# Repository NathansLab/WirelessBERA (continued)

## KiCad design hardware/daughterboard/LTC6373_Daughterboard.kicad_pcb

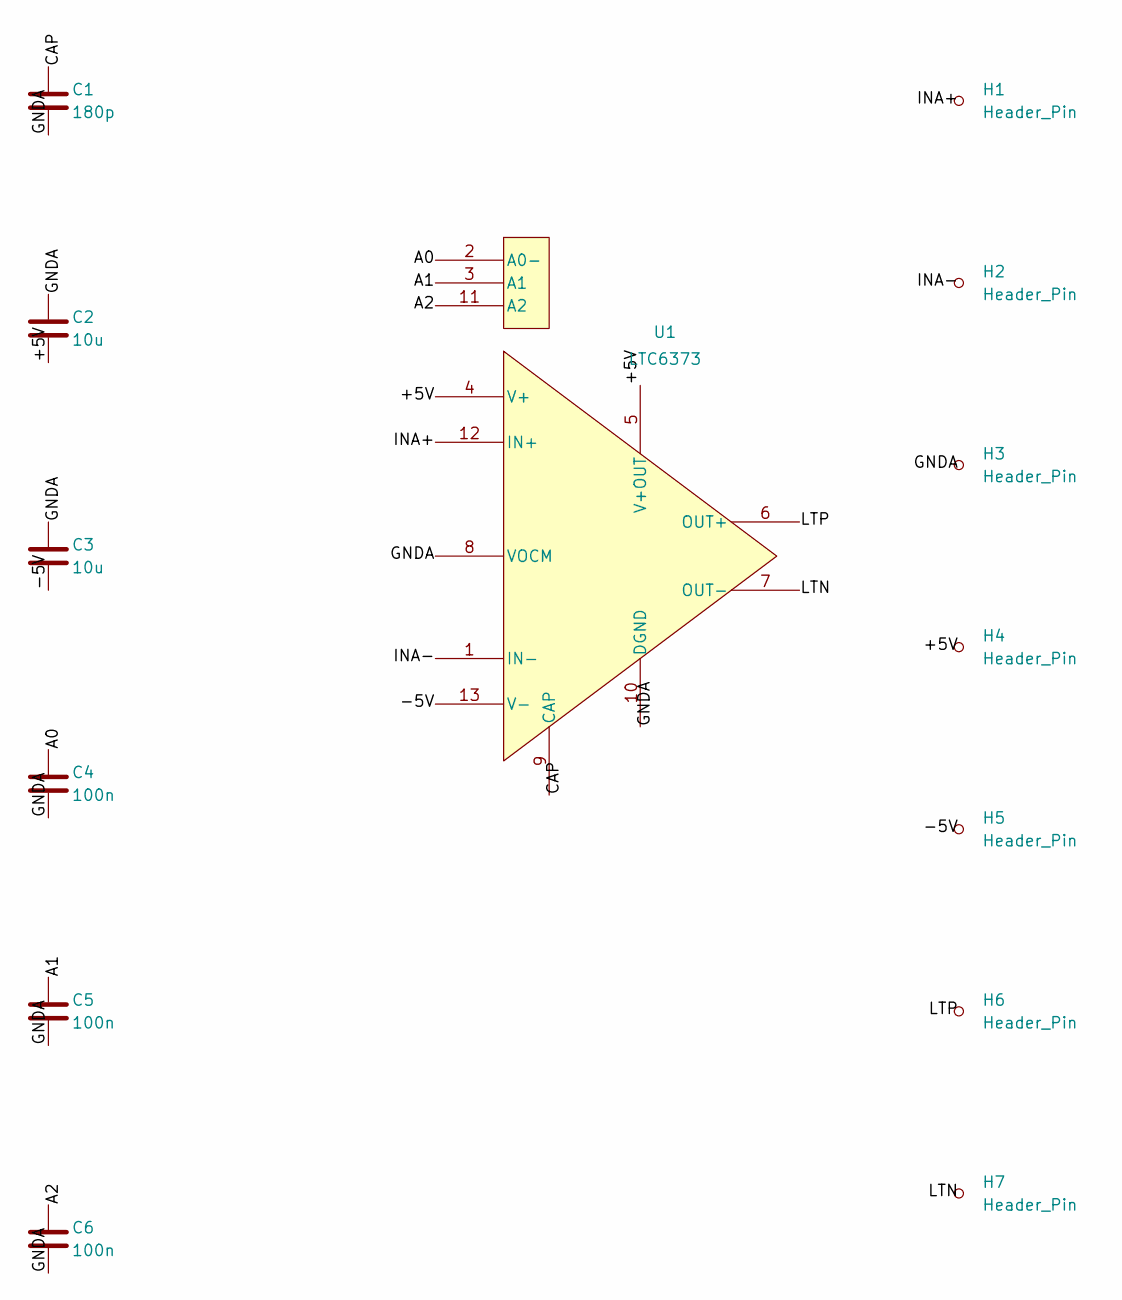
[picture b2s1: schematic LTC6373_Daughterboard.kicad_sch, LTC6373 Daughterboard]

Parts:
C1: 180p; C_0603_1608Metric
C2, C3: 10u; C_0603_1608Metric
C4, C5, C6: 100n; C_0603_1608Metric
H1, H2, H3, H4, H5, H6, H7: Header_Pin; TestPoint_Loop_D2.60mm_Drill0.9mm_Beaded
U1: LTC6373; LTC6373_DFN-12

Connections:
+5V: C2.2, H4.1 (1_1), U1.4 (V+), U1.5 (V+OUT)
-5V: C3.2, H5.1 (1_1), U1.13 (V-)
A0: C4.1, U1.2 (A0-)
A1: C5.1, U1.3 (A1)
A2: C6.1, U1.11 (A2)
CAP: C1.1, U1.9 (CAP)
GNDA: C1.2, C2.1, C3.1, C4.2, C5.2, C6.2, H3.1 (1_1), U1.8 (VOCM), U1.10 (DGND)
INA+: H1.1 (1_1), U1.12 (IN+)
INA-: H2.1 (1_1), U1.1 (IN-)
LTN: H7.1 (1_1), U1.7 (OUT-)
LTP: H6.1 (1_1), U1.6 (OUT+)

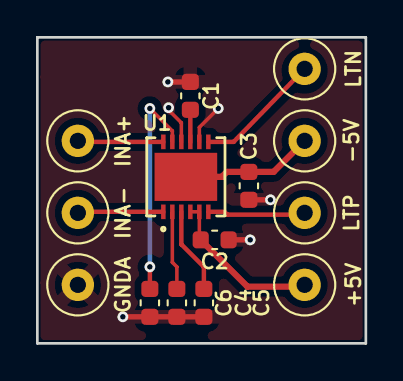
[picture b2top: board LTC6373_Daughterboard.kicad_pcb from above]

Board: 2 copper layers, 18.2 x 17.0 mm, 14 parts (0 on the bottom side), 11 nets.

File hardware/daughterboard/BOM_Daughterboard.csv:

"Refs","Value","Footprint","Qty","DNP"
"C1","180p","Capacitor_SMD:C_0603_1608Metric","1",""
"C2","10u","Capacitor_SMD:C_0603_1608Metric","1",""
"C3","10u","Capacitor_SMD:C_0603_1608Metric","1",""
"C4","100n","Capacitor_SMD:C_0603_1608Metric","1",""
"C5","100n","Capacitor_SMD:C_0603_1608Metric","1",""
"C6","100n","Capacitor_SMD:C_0603_1608Metric","1",""
"H1","Header_Pin","TestPoint:TestPoint_Loop_D2.60mm_Drill0.9mm_Beaded","1",""
"H2","Header_Pin","TestPoint:TestPoint_Loop_D2.60mm_Drill0.9mm_Beaded","1",""
"H3","Header_Pin","TestPoint:TestPoint_Loop_D2.60mm_Drill0.9mm_Beaded","1",""
"H4","Header_Pin","TestPoint:TestPoint_Loop_D2.60mm_Drill0.9mm_Beaded","1",""
"H5","Header_Pin","TestPoint:TestPoint_Loop_D2.60mm_Drill0.9mm_Beaded","1",""
"H6","Header_Pin","TestPoint:TestPoint_Loop_D2.60mm_Drill0.9mm_Beaded","1",""
"H7","Header_Pin","TestPoint:TestPoint_Loop_D2.60mm_Drill0.9mm_Beaded","1",""
"U1","LTC6373","BERA Project Specific Footprints:LTC6373_DFN-12","1",""

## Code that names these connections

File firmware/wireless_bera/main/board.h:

/*
 * board.h - Wireless BERA v1.0 hardware description.
 *
 * Single source of truth for every pin, bus address and electrical constant.
 * Everything here was derived from hardware/WirelessBERA.kicad_sch (netlist
 * extracted 2026-09-17) and the part datasheets in hardware/datasheets/.
 * If the schematic changes, change this file - nothing else should hard-code
 * a GPIO number.
 *
 * Board overview
 * --------------
 *   Electrode jack J6 (TRS)  ->  LTC6373 PGIA (U10, G = 0.25..16)
 *                            ->  TAC5212 IN2P/IN2M   (ADC channel 2, DC-coupled)
 *   MEMS mic MK1 (IM73A135)  ->  TAC5212 IN1P/IN1M   (ADC channel 1, AC-coupled)
 *   TAC5212 OUT1P / OUT2P    ->  stimulus jack J11 (TRS, AC-coupled, OUTxM to GND)
 *   OPA376 (U9)              ->  driven-right-leg feedback to J6 tip
 *
 * The ESP32-S3 is the I2S clock master; the TAC5212 recovers its internal
 * clocks from BCLK through its PLL (there is no MCLK line on this board).
 */
#pragma once

#include "driver/gpio.h"
#include "hal/i2s_types.h"
#include "hal/adc_types.h"

#ifdef __cplusplus
extern "C" {
#endif

/* ------------------------------------------------------------------ */
/* Identity                                                            */
/* ------------------------------------------------------------------ */
#define BOARD_NAME              "Wireless BERA"
#define BOARD_HW_REV            "1.0"
#define FIRMWARE_VERSION        "2.0.0"

/* ------------------------------------------------------------------ */
/* I2C control bus (TAC5212 + TPS65132W)                               */
/* ------------------------------------------------------------------ */
#define BOARD_I2C_PORT          I2C_NUM_0
#define BOARD_I2C_SDA_GPIO      GPIO_NUM_4      /* U7.4  <-> U11.8, U5.7   */
#define BOARD_I2C_SCL_GPIO      GPIO_NUM_5      /* U7.5  <-> U11.7, U5.8   */
#define BOARD_I2C_HZ            400000          /* R30/R31 = 10k to +3.5V  */

/* TAC5212 ADDR pin (U11.13) is shorted to GNDD -> 7-bit address 0x50.
 * (The five MSBs of the address are fixed at 0b10100 in the silicon.)     */
#define TAC5212_I2C_ADDR        0x50
#define TPS65132_I2C_ADDR       0x3E

/* ------------------------------------------------------------------ */
/* I2S audio serial interface to the TAC5212                           */
/* ------------------------------------------------------------------ */
/* Net names in the schematic are from the CODEC's point of view:
 *   net I2S_DOUT = TAC5212 DOUT (pin 4) -> ESP GPIO7  => ESP receives here
 *   net I2S_DIN  = TAC5212 DIN  (pin 5) <- ESP GPIO6  => ESP transmits here   */
#define BOARD_I2S_PORT          I2S_NUM_0
#define BOARD_I2S_BCLK_GPIO     GPIO_NUM_16     /* U7.9  -> U11.2 BCLK     */
#define BOARD_I2S_FSYNC_GPIO    GPIO_NUM_15     /* U7.8  -> U11.3 FSYNC    */
#define BOARD_I2S_DIN_GPIO      GPIO_NUM_7      /* ESP in  <- codec DOUT   */
#define BOARD_I2S_DOUT_GPIO     GPIO_NUM_6      /* ESP out -> codec DIN    */

/* ------------------------------------------------------------------ */
/* LTC6373 programmable-gain instrumentation amplifier (U10)           */
/* ------------------------------------------------------------------ */
/* Logic levels are referenced to the LTC6373 DGND pin, which is tied to
 * GNDA on this board: VIL <= 0.6 V, VIH >= 1.5 V. The ESP drives 3.5 V
 * CMOS through 10 k series resistors (R35/R36/R37), so both are satisfied.
 * All three pins have internal pull-downs, so a floating ESP pin (e.g. at
 * reset, before gpio config) selects G = 16.
 *
 * HARDWARE CAVEAT on the current v1.0 build: R35, R36 and R37 are NOT fitted,
 * so these GPIOs are not connected to U10 at all. The amplifier's A2/A1/A0
 * pins float, its internal pull-downs take them to DGND, and it therefore
 * runs permanently at G = 16. The driver below still toggles the pins (and
 * they are correct), but the gain will not change until those three resistors
 * are populated. Set BOARD_PGIA_RESISTORS_FITTED to 1 once they are.        */
#define BOARD_PGIA_RESISTORS_FITTED  0
#define BOARD_PGIA_FIXED_GAIN        16.0f   /* while the above is 0 */
#define BOARD_PGIA_A0_GPIO      GPIO_NUM_8      /* U7.12 -> R35 -> U10.2   */
#define BOARD_PGIA_A1_GPIO      GPIO_NUM_18     /* U7.11 -> R36 -> U10.3   */
#define BOARD_PGIA_A2_GPIO      GPIO_NUM_17     /* U7.10 -> R37 -> U10.11  */

/* ------------------------------------------------------------------ */
/* Status LED D2 (green, 0603) - active high through R32 = 330 R        */
/* ------------------------------------------------------------------ */
#define BOARD_LED_GPIO          GPIO_NUM_21     /* U7.23 -> R32 -> D2      */

/* ------------------------------------------------------------------ */
/* Battery sense - R23/R24 = 10k/10k divider from V_BAT                 */
/* ------------------------------------------------------------------ */
#define BOARD_VBAT_GPIO         GPIO_NUM_1      /* U7.39                   */
#define BOARD_VBAT_ADC_UNIT     ADC_UNIT_1
#define BOARD_VBAT_ADC_CHANNEL  ADC_CHANNEL_0   /* GPIO1 = ADC1_CH0        */
#define BOARD_VBAT_DIVIDER      2.0f            /* (R23 + R24) / R24       */

/* Single-cell Li-Ion, charged by the BQ24074 (U2) to 4.2 V. */
#define BOARD_VBAT_FULL_MV      4200
#define BOARD_VBAT_EMPTY_MV     3300

/* ------------------------------------------------------------------ */
/* microSD card J4 - SDMMC slot 1, 4-bit, card VDD = +3.5V_ESP          */
/* ------------------------------------------------------------------ */
/* Not used by this firmware version yet, recorded here so that nobody
 * re-assigns these pins by accident. D2 sits on GPIO44 (= U0RXD); that is
 * fine because the console runs over the native USB-Serial/JTAG port.      */
#define BOARD_SD_CLK_GPIO       GPIO_NUM_40
#define BOARD_SD_CMD_GPIO       GPIO_NUM_41
#define BOARD_SD_D0_GPIO        GPIO_NUM_39
#define BOARD_SD_D1_GPIO        GPIO_NUM_38
#define BOARD_SD_D2_GPIO        GPIO_NUM_44
#define BOARD_SD_D3_GPIO        GPIO_NUM_42

/* ------------------------------------------------------------------ */
/* Buttons                                                             */
/* ------------------------------------------------------------------ */
#define BOARD_BOOT_GPIO         GPIO_NUM_0      /* SW3, active low         */

/* ------------------------------------------------------------------ */
/* Analog front-end constants                                          */
/* ------------------------------------------------------------------ */
/* LTC6373 differential output common mode, set by R40 (4.99k to +3.3V_TAC_A)
 * and R43 (10k to GNDA): VOCM = 3.3 * 10 / 14.99 = 2.20 V.
 * The TAC5212 IN2x pins are DC-coupled to this, so ADC channel 2 must run in
 * rail-to-rail common-mode tolerance mode (CM_TOL = 2).                    */
#define BOARD_PGIA_VOCM_V       2.20f

/* MEMS microphone MK1 (IM73A135V01) is powered from the codec MICBIAS pin.
 * Its ABSOLUTE MAXIMUM supply is 3.0 V, so MICBIAS must stay at VREF
 * (2.75 V) - never switch MICBIAS to the "bypass to AVDD" (3.3 V) setting. */
#define BOARD_MIC_VDD_MAX_V     3.0f
#define BOARD_MIC_SENS_DBV      (-38.0f)        /* dBV @ 94 dB SPL, 1 kHz  */

/* TPS65132W (U5) pre-programmed defaults are +/-5.4 V. The TPS7A39 dual LDO
 * (U4) downstream needs roughly 250 mV of headroom for its +/-5 V outputs,
 * so do not program the rails below about 5.3 V.                           */
#define BOARD_RAIL_DEFAULT_V    5.4f
#define BOARD_RAIL_MIN_SAFE_V   5.3f

#ifdef __cplusplus
}
#endif

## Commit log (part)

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2026-05-30 v1.0 Release: Stacked daughterboard alignment & clean renderings
2026-06-03 Changed Pinheader and found a Problem with V0CM.
2026-06-03 Release: First PCB manufacturing batch. Fixed U10 thermal via short, exempted fiducials from solder mask margin override rule, adjusted R22 label, and updated all manufacturing files.
2026-06-03 Add Mouser QuickPaste format text file.
2026-06-03 Version 1.0 ordered at Aisler. Waiting for PCBs to arrive.
2026-06-03 BOM Update: Replace C48 and C53 with Mouser part GRM188R61C106MA73J and update all exports.
